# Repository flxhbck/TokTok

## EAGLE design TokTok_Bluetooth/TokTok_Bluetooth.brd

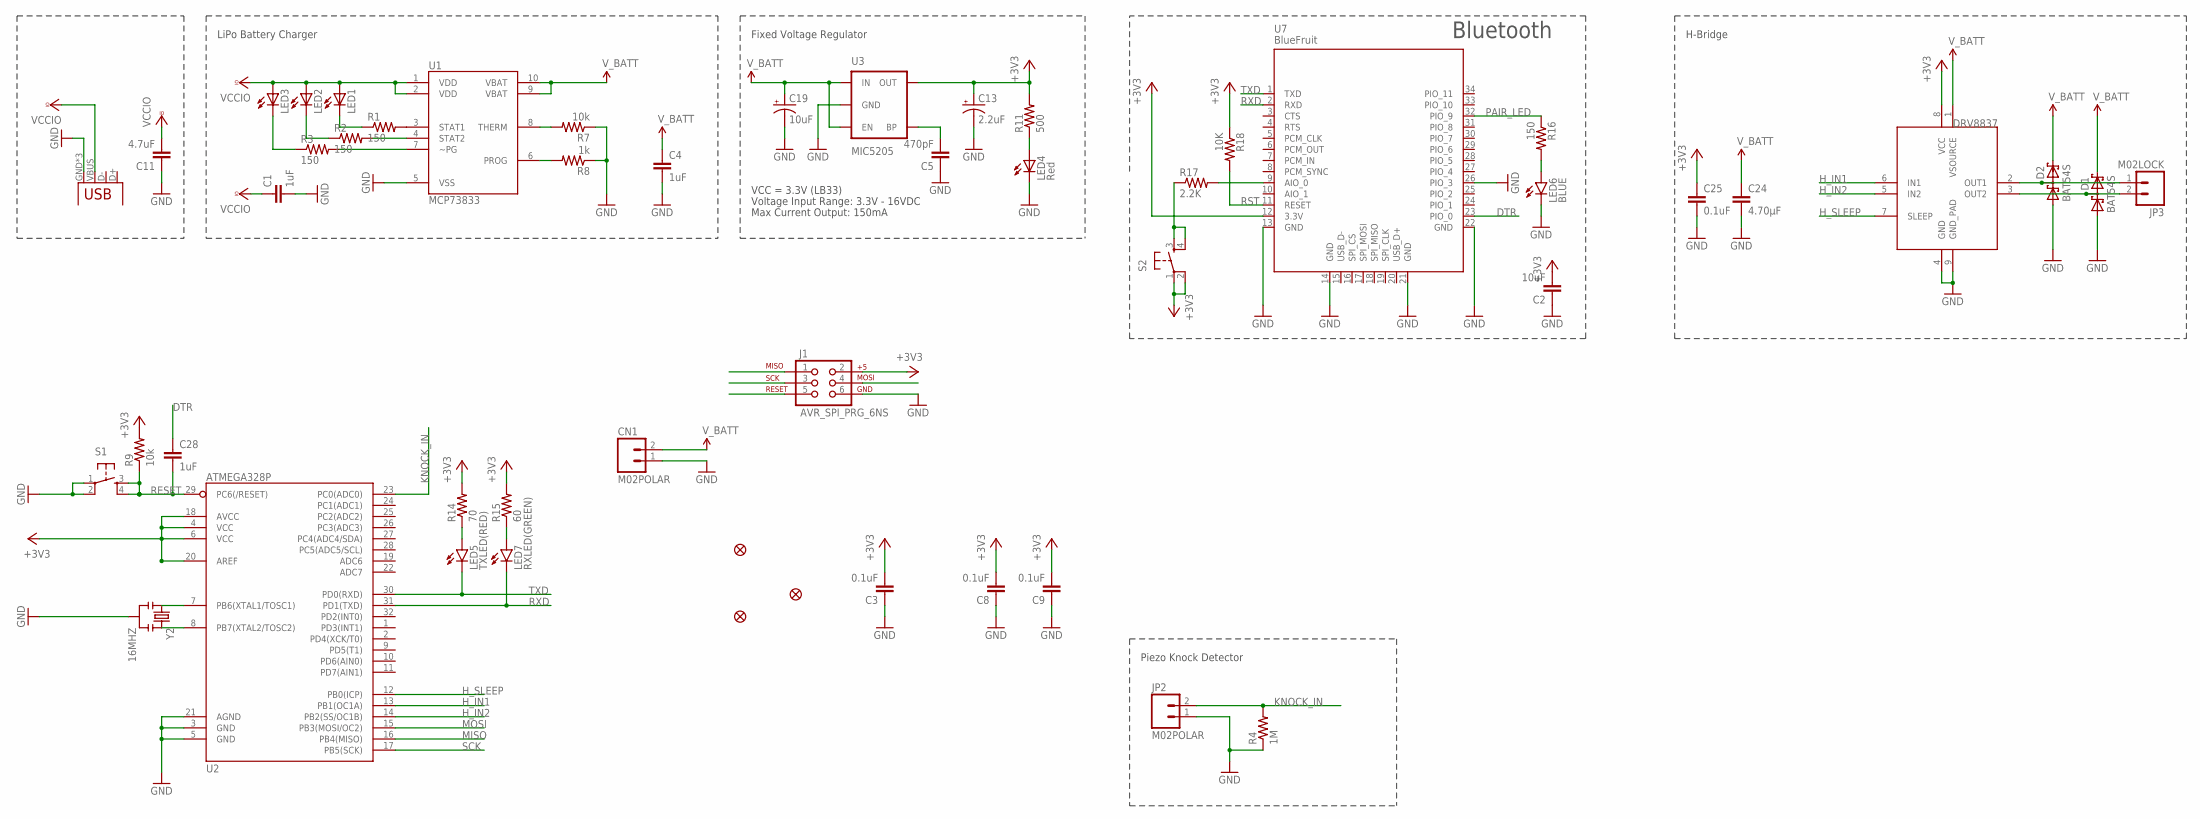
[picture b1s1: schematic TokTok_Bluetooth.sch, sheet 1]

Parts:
C1, C4: 1uF; C0805K
C2: 10uF; 0805
C3, C8, C9: 0.1uF; C0805K
C5: 470pF; 0805
C11: 4.7uF; C0805K
C13: 2.2uF; EIA3216
C19: 10uF; EIA3216
C24: 4.70µF; 0805
C25: 0.1uF; 0805
C28: 1uF; 0805
CN1: M02POLAR; MOLEX-1X2
D1, D2: BAT54S; SOT23
FID1, FID2, FID3: FIDUCIAL""; FIDUCIAL_1MM
IC2: DRV8837; WSON-8
J1: AVR_SPI_PRG_6NS; 2X3-NS
JP1: USB-MICROB
JP2: M02POLAR; MOLEX-1X2
JP3: M02LOCK; 1X02_LOCK
LED1, LED2, LED3: LEDCHIPLED_1206; CHIPLED_1206
LED4: Red; LED-1206
LED5: TXLED(RED); LED-1206
LED6: BLUE; LED-1206
LED7: RXLED(GREEN); LED-1206
R1, R2, R3: 150; M0805
R4: 1M; 0805
R7, R9: 10k; M0805
R8: 1k; M0805
R11: 500; 0805
R14: 70; 0805
R15: 60; 0805
R16: 150; 0805
R17: 2.2K; 0805
R18: 10K; 0805
S1, S2: TAC_SWITCHSMD; TACTILE-SWITCH-SMD
U1: MCP73833; MSOP-10
U2: ATMEGA328P; TQFP32-08
U3: MIC5205; SOT23-5
U7: BlueFruit; BLUETOOTH_MODULE
Y2: 16MHZ; RESONATOR-SMD

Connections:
+3V3: C2.2, C3.2, C8.2, C9.2, C13.A (+), C25.1, IC2.8 (VCC), J1.2, R9.2, R11.2, R14.2, R15.2, R18.1, S2.1, S2.2, U2.4 (VCC), U2.6 (VCC), U2.18 (AVCC), U2.20 (AREF), U3.5 (OUT), U7.12 (3.3V)
DTR: C28.1, U7.23 (PIO_0)
GND: C1.2, C2.1, C3.1, C4.2, C5.1, C8.1, C9.1, C11.1, C13.C (-), C19.C (-), C24.2, C25.2, CN1.1, D1.1 (A1), D2.1 (A1), IC2.4 (GND), IC2.9 (GND_PAD), J1.6, JP1.GND, JP1.MT1 (GND), JP1.MT2 (GND), JP2.1, LED4.C, LED6.C, R4.1, R7.1, R8.1, S1.1, S1.2, U1.5 (VSS), U2.3 (GND), U2.5 (GND), U2.21 (AGND), U3.2 (GND), U7.13 (GND), U7.14 (GND), U7.21 (GND), U7.22 (GND), U7.26 (PIO_3), Y2.2
H_IN1: IC2.6 (IN1), U2.13 (PB1(OC1A))
H_IN2: IC2.5 (IN2), U2.14 (PB2(SS/OC1B))
H_SLEEP: IC2.7 (SLEEP), U2.12 (PB0(ICP))
KNOCK_IN: JP2.2, R4.2, U2.23 (PC0(ADC0))
MISO: J1.1, U2.16 (PB4(MISO))
MOSI: J1.4, U2.15 (PB3(MOSI/OC2))
unnamed: R7.2, U1.8 (THERM)
unnamed: U2.7 (PB6(XTAL1/TOSC1)), Y2.1
unnamed: R1.2, U1.3 (STAT1)
unnamed: R2.2, U1.4 (STAT2)
unnamed: R3.2, U1.7 (~PG)
unnamed: LED1.C, R1.1
unnamed: LED2.C, R2.1
unnamed: LED3.C, R3.1
unnamed: U2.8 (PB7(XTAL2/TOSC2)), Y2.3
unnamed: R8.2, U1.6 (PROG)
unnamed: R17.1, S2.3, S2.4
unnamed: R17.2, U7.9 (AIO_0)
unnamed: C5.2, U3.4 (BP)
unnamed: LED5.A, R14.1
unnamed: LED7.A, R15.1
unnamed: LED6.A, R16.2
unnamed: D2.3 (C1A2), IC2.2 (OUT1), JP3.1
unnamed: D1.3 (C1A2), IC2.3 (OUT2), JP3.2
unnamed: LED4.A, R11.1
PAIR_LED: R16.1, U7.32 (PIO_9)
RESET: C28.2, J1.5, R9.1, S1.3, S1.4, U2.29 (PC6(/RESET))
RST: R18.2, U7.11 (RESET)
RXD: LED7.C, U2.31 (PD1(TXD)), U7.2 (RXD)
SCK: J1.3, U2.17 (PB5(SCK))
TXD: LED5.C, U2.30 (PD0(RXD)), U7.1 (TXD)
VCCIO: C1.1, C11.2, JP1.VBUS, LED1.A, LED2.A, LED3.A, U1.1 (VDD), U1.2 (VDD)
V_BATT: C4.1, C19.A (+), C24.1, CN1.2, D1.2 (C2), D2.2 (C2), IC2.1 (VSOURCE), U1.9 (VBAT), U1.10 (VBAT), U3.1 (IN), U3.3 (EN)

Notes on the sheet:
Max Current Output: 150mA
VCC = 3.3V (LB33)
Voltage Input Range: 3.3V - 16VDC
Fixed Voltage Regulator
LiPo Battery Charger
H-Bridge
Piezo Knock Detector
Bluetooth

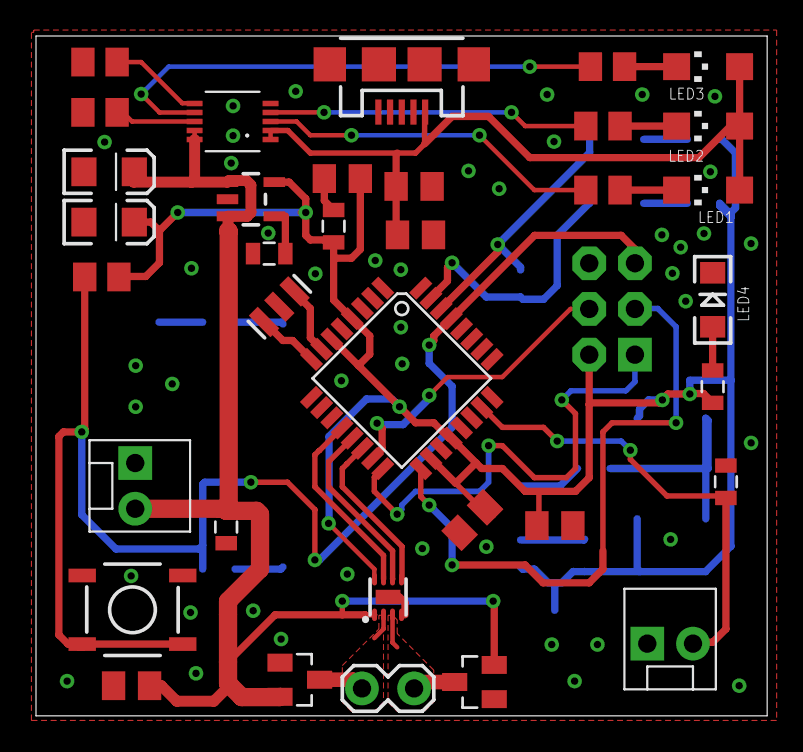
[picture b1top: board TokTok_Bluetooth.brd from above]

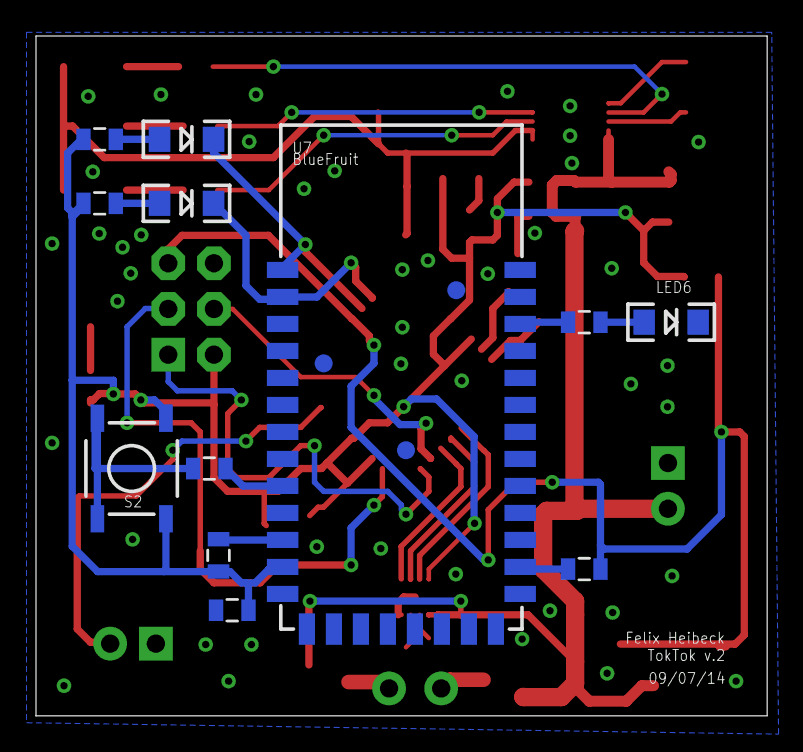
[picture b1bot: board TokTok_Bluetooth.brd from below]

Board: 2 copper layers, 40.6 x 37.8 mm, 51 parts (15 on the bottom side), 36 nets.

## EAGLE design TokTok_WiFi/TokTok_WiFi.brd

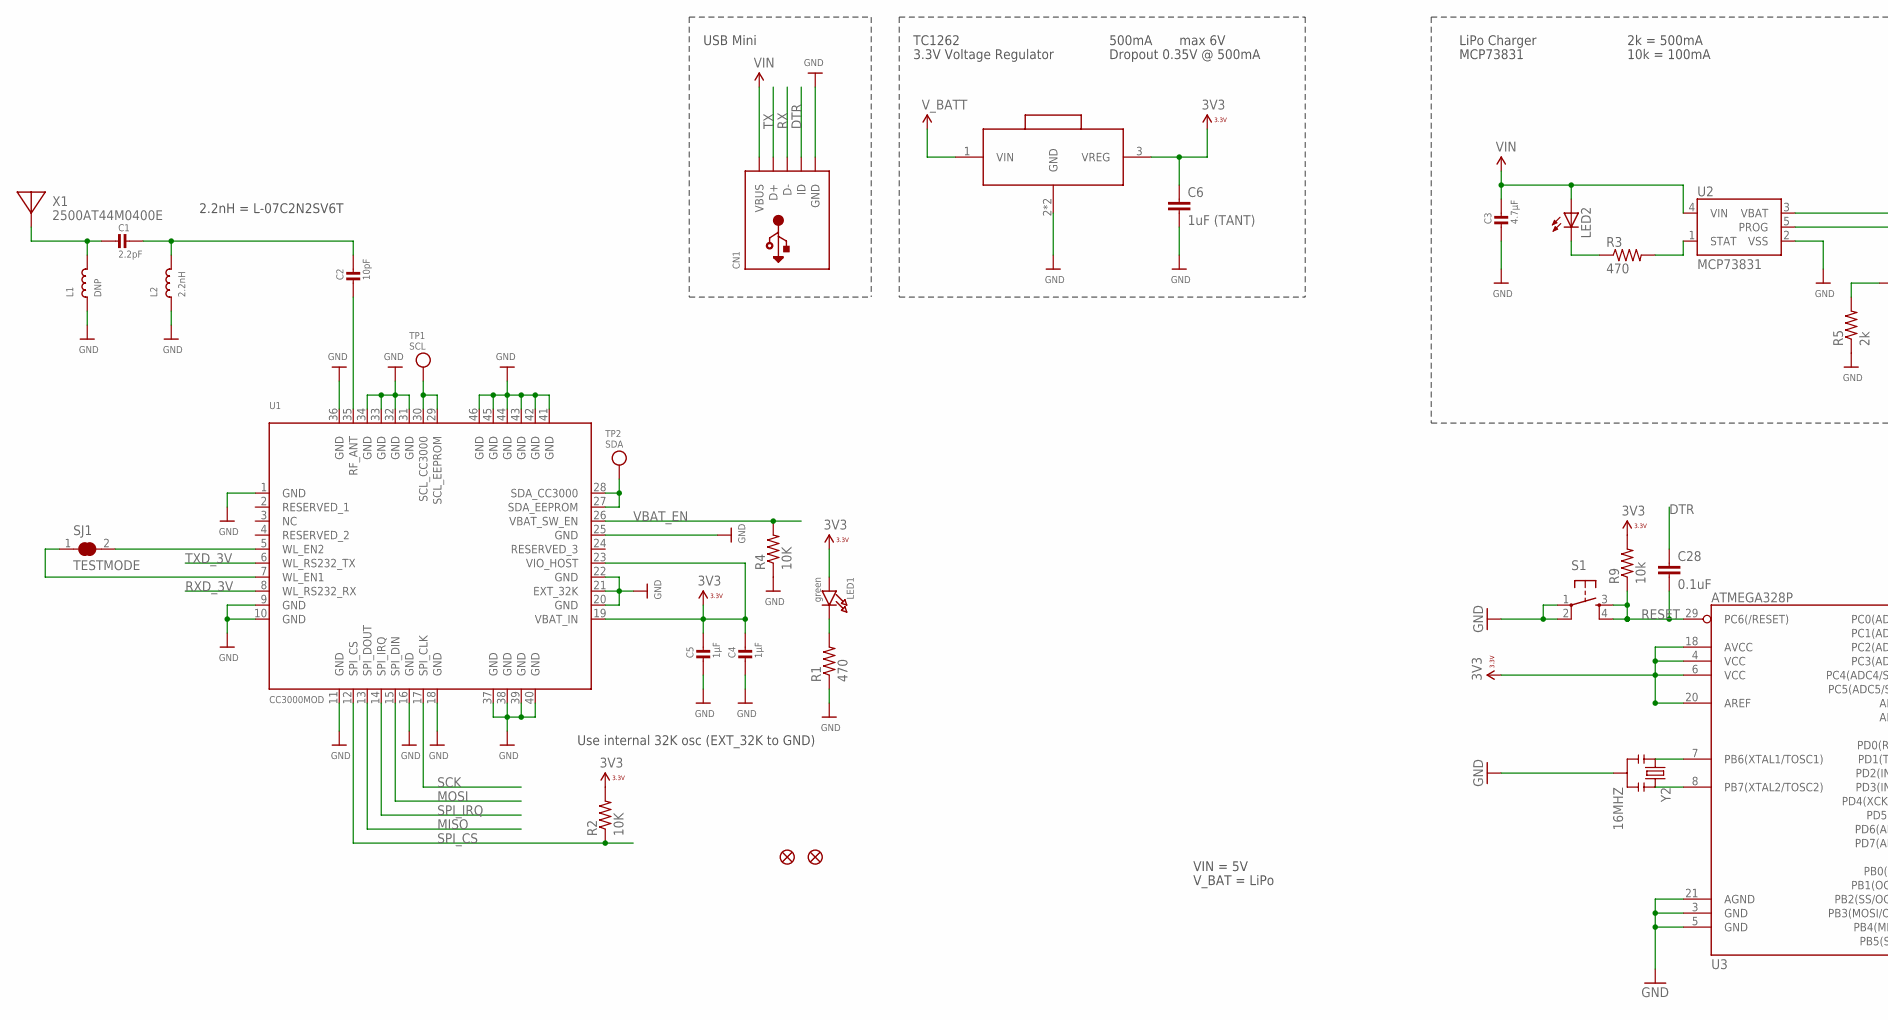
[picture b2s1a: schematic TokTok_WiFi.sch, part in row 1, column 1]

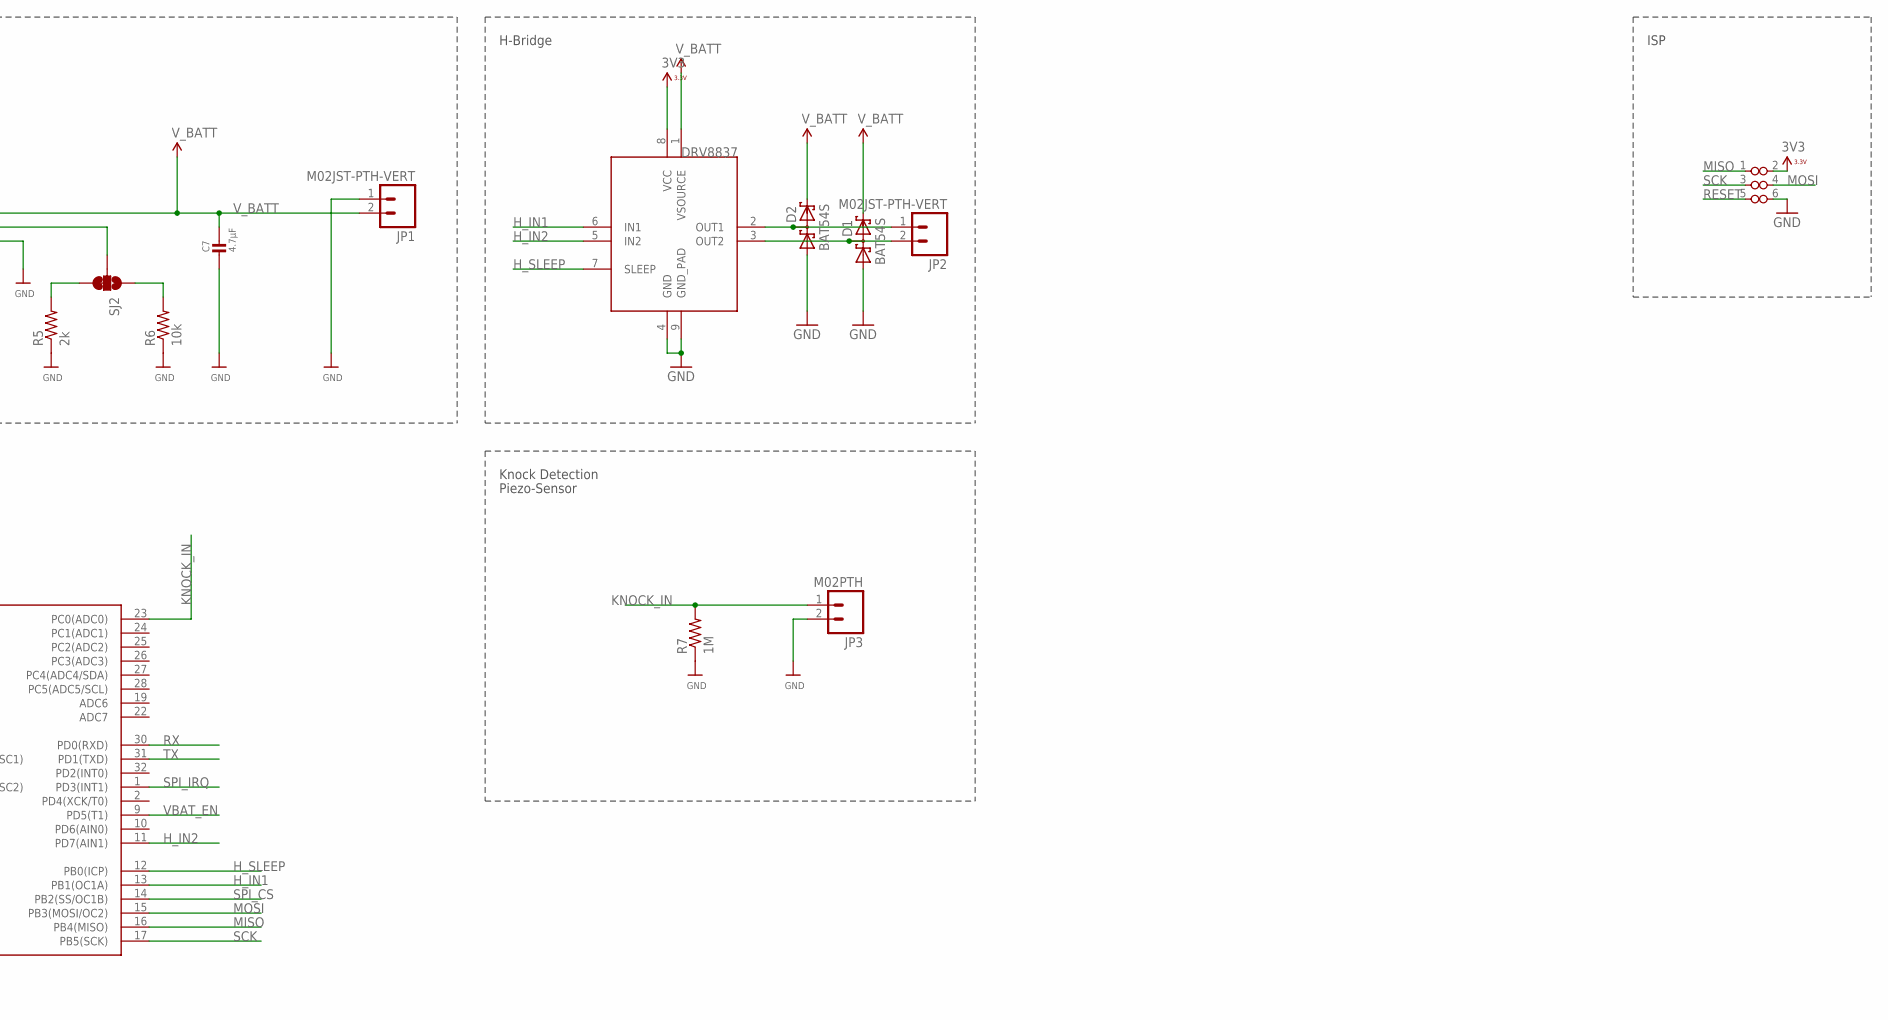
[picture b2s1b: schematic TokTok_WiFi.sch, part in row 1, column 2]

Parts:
C1: 2.2pF; _0402
C2: 10pF; _0402
C3, C7: 4.7µF; _0805MP
C4, C5: 1µF; _0805MP
C6: 1uF (TANT); 1206
C28: 0.1uF; 0805
CN1: USBMINIB; USB-MINIB
D1, D2: BAT54S; SOT23
FID1, FID3: FIDUCIAL""; FIDUCIAL_1MM
IC2: DRV8837; WSON-8
JP1, JP2: M02JST-PTH-VERT; JST-2-PTH-VERT
JP3: M02PTH; 1X02
L1: DNP; _0402
L2: 2.2nH; _0402
LED1: green; CHIPLED_0805_NOOUTLINE
LED2: LEDCHIP-LED0805; CHIP-LED0805
R1, R3: 470; 0805
R2, R4: 10K; 0805
R5: 2k; 0805
R6: 10k; 0805
R7: 1M; 0805
R9: 10k; M0805
S1: TAC_SWITCHSMD; TACTILE-SWITCH-SMD
SJ1: TESTMODE; SOLDERJUMPER_CLOSEDWIRE
SJ2: JUMPER-PAD-3-2OF3_NC_BY_TRACE_SMALL; PAD-JUMPER-3-2OF3_NC_BY_TRACE_YES_SILK_FULL_BOX
TP1: SCL; TESTPOINT_PAD_1MM
TP2: SDA; TESTPOINT_PAD_1MM
U1: CC3000MOD
U2: MCP73831; SOT23-5
U3: ATMEGA328P; TQFP32-08
U$3: TC1262; SOT223
U$36: ISP_POGO; POGO_ISP
X1: 2500AT44M0400E; ANT_2500AT44M0400
Y2: 16MHZ; RESONATOR-SMD

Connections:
3V3: C4.1, C5.1, C6.1, IC2.8 (VCC), LED1.A, R2.2, R9.2, U1.19 (VBAT_IN), U1.23 (VIO_HOST), U3.4 (VCC), U3.6 (VCC), U3.18 (AVCC), U3.20 (AREF), U$3.3 (VREG), U$36.2 (VCC)
DTR: C28.1, CN1.ID
GND: C3.2, C4.2, C5.2, C6.2, C7.2, CN1.GND, D1.1 (A1), D2.1 (A1), IC2.4 (GND), IC2.9 (GND_PAD), JP1.1, JP3.2, L1.1, L2.1, R1.1, R4.1, R5.1, R6.1, R7.1, S1.1, S1.2, U1.1 (GND), U1.9 (GND), U1.10 (GND), U1.11 (GND), U1.16 (GND), U1.18 (GND), U1.20 (GND), U1.21 (EXT_32K), U1.22 (GND), U1.25 (GND), U1.31 (GND), U1.32 (GND), U1.33 (GND), U1.34 (GND), U1.36 (GND), U1.37 (GND), U1.38 (GND), U1.39 (GND), U1.40 (GND), U1.41 (GND), U1.42 (GND), U1.43 (GND), U1.44 (GND), U1.45 (GND), U1.46 (GND), U2.2 (VSS), U3.3 (GND), U3.5 (GND), U3.21 (AGND), U$3.2 (GND), U$3.4 (GND), U$36.6 (GND), Y2.2
H_IN1: IC2.6 (IN1), U3.13 (PB1(OC1A))
H_IN2: IC2.5 (IN2), U3.11 (PD7(AIN1))
H_SLEEP: IC2.7 (SLEEP), U3.12 (PB0(ICP))
KNOCK_IN: JP3.1, R7.2, U3.23 (PC0(ADC0))
MISO: U1.13 (SPI_DOUT), U3.16 (PB4(MISO)), U$36.1 (MISO)
MOSI: U1.15 (SPI_DIN), U3.15 (PB3(MOSI/OC2)), U$36.4 (MOSI)
unnamed: C1.2, L1.2, X1.FEED
unnamed: C1.1, C2.1, L2.2
unnamed: R3.2, U2.1 (STAT)
unnamed: C2.2, U1.35 (RF_ANT)
unnamed: SJ1.2, U1.5 (WL_EN2)
unnamed: SJ1.1, U1.7 (WL_EN1)
unnamed: LED1.C, R1.2
unnamed: LED2.C, R3.1
unnamed: SJ2.2, U2.5 (PROG)
unnamed: U3.7 (PB6(XTAL1/TOSC1)), Y2.1
unnamed: R5.2, SJ2.3
unnamed: R6.2, SJ2.1
unnamed: U3.8 (PB7(XTAL2/TOSC2)), Y2.3
unnamed: D2.3 (C1A2), IC2.2 (OUT1), JP2.1
unnamed: D1.3 (C1A2), IC2.3 (OUT2), JP2.2
RESET: C28.2, R9.1, S1.3, S1.4, U3.29 (PC6(/RESET)), U$36.5 (RESET)
RX: CN1.D-, U3.30 (PD0(RXD))
RXD_3V: U1.8 (WL_RS232_RX)
SCK: U1.17 (SPI_CLK), U3.17 (PB5(SCK)), U$36.3 (SCK)
SCL_3V: TP1.P$1, U1.29 (SCL_EEPROM), U1.30 (SCL_CC3000)
SDA_3V: TP2.P$1, U1.27 (SDA_EEPROM), U1.28 (SDA_CC3000)
SPI_CS: R2.1, U1.12 (SPI_CS), U3.14 (PB2(SS/OC1B))
SPI_IRQ: U1.14 (SPI_IRQ), U3.1 (PD3(INT1))
TX: CN1.D+, U3.31 (PD1(TXD))
TXD_3V: U1.6 (WL_RS232_TX)
VBAT_EN: R4.2, U1.26 (VBAT_SW_EN), U3.9 (PD5(T1))
VIN: C3.1, CN1.VBUS, LED2.A, U2.4 (VIN)
V_BATT: C7.1, D1.2 (C2), D2.2 (C2), IC2.1 (VSOURCE), JP1.2, U2.3 (VBAT), U$3.1 (VIN)

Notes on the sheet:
Use internal 32K osc (EXT_32K to GND)
VIN = 5V
V_BAT = LiPo
2.2nH = L-07C2N2SV6T
ISP
H-Bridge
TC1262
3.3V Voltage Regulator
500mA
max 6V
Dropout 0.35V @ 500mA
USB Mini
Knock Detection
Piezo-Sensor
LiPo Charger
MCP73831
2k = 500mA
10k = 100mA

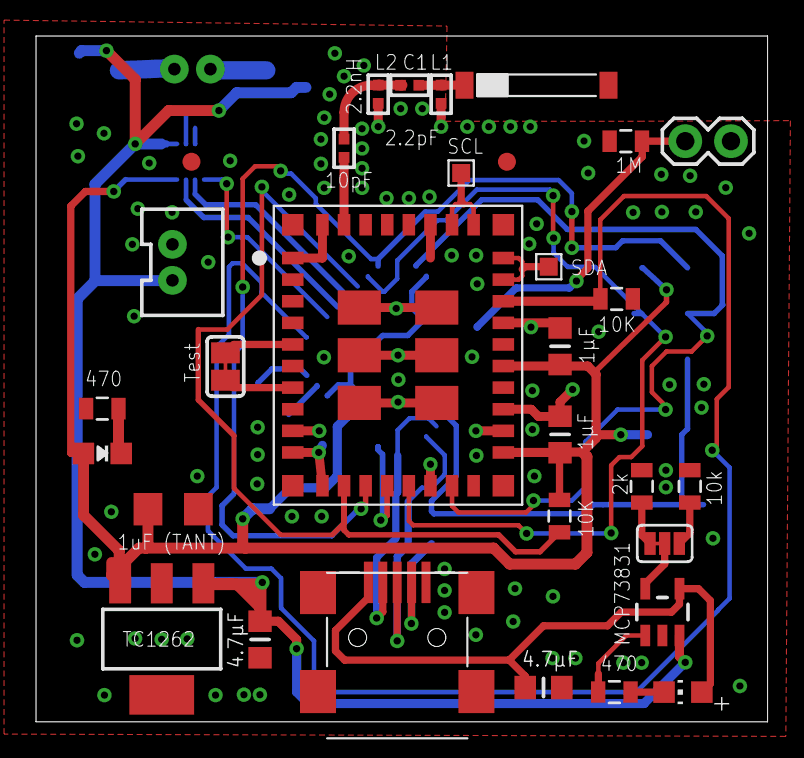
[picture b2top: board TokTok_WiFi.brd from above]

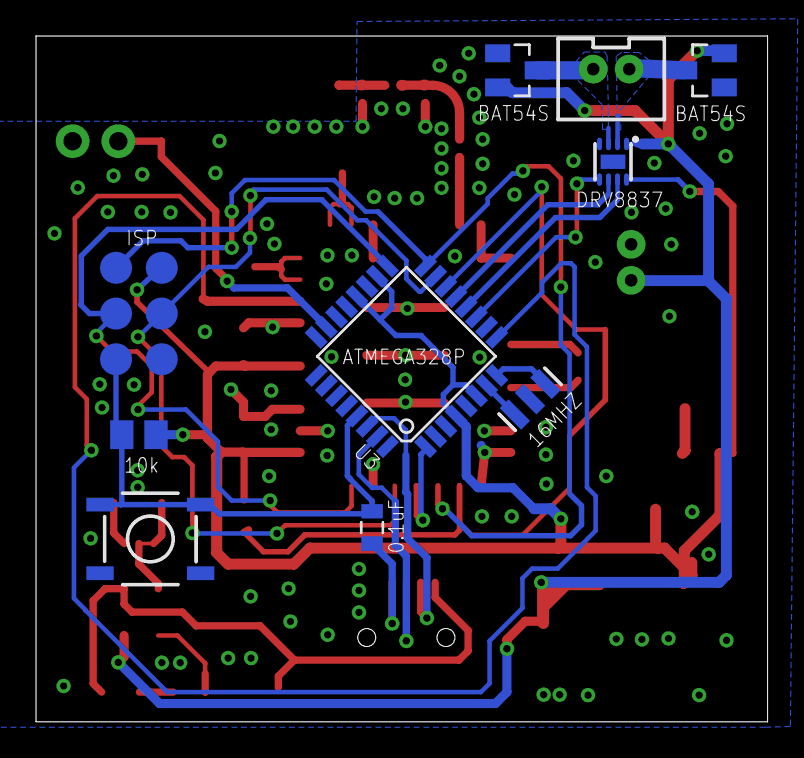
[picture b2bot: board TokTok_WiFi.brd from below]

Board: 2 copper layers, 40.6 x 38.1 mm, 41 parts (10 on the bottom side), 35 nets.

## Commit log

2015-02-18 create

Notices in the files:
parts and their libraries:
SparkFun-PowerIC: Licensing: CC v3.0 Share-Alike You are welcome to use this library for commercial purposes.
microbuilder: This work is placed in the public domain, and may be freely used for commercial and non-commercial work with the following conditions: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
